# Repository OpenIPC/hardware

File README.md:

![OpenIPC logo][logo]

## OpenIPC hardware developments 

[][telegram]

### A collection of hardware developments by the OpenIPC team

- [One of the open board for OpenIPC](board_hi3516ev200)
- [8812AU module dock board for camera,input 6V@2A max and 28V@ 3A max](/module_38x38_r8812au_6v2a)
- [WIFI board for stacking on 20mm square hole flight controller for FPV](WIFI-BOARD)

### A collection of 3D models for use in OpenIPC projects

- [OpenIPC models on Printables site](https://www.printables.com/search/models?q=tag:openipc)
- [5 inch racer drone equipped with OpenIPC](OpenIPC-5inchRacer)

### Measure the output of RTL8812AU.
- [Measure the output of RTL8812AU](spectram)

More information about the [project][project] is available in our [website][website]
and on the [wiki][wiki].

<p align="center">

</p>

[firmware]: https://github.com/openipc/firmware/
[logo]: https://openipc.org/assets/openipc-logo-black.svg
[mit]: https://opensource.org/license/mit/
[opencollective]: https://opencollective.com/openipc
[paypal]: https://www.paypal.com/donate/?hosted_button_id=C6F7UJLA58MBS
[project]: https://github.com/openipc/
[telegram]: https://t.me/OpenIPC
[website]: https://openipc.org/
[wiki]: https://github.com/openipc/wiki/

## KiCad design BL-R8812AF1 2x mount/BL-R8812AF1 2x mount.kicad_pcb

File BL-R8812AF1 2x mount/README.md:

## A Radxa Zero 3W stackable double BL-R8812AF1 board

# Note this board has problems!

## The board is often not recognised by the Radxa on boot and needs re-plugging before it is detected by the Radxa. Sometimes it has this problem then powered by a BEC and not when powered from USB. I think this is an issue with this USB hub chip, and this issue has been reproduced by another user. I will update this page if/when a fix is found.

### The board integrates an SL2.1A USB hub chip which splits a single USB interface into 4 interfaces: two are used by the WiFi modules, and two additional ones are broken out for use with anything else (keyboard for configuration, USB stick, more WiFi dongles etc.).

## HOW TO MAKE
### You can order the PCB by sending the gerber files in the .zip to a PCB manufacturer. I have also included the source Kicad project files if you want to make any modifications.

<p align="center">

</p>

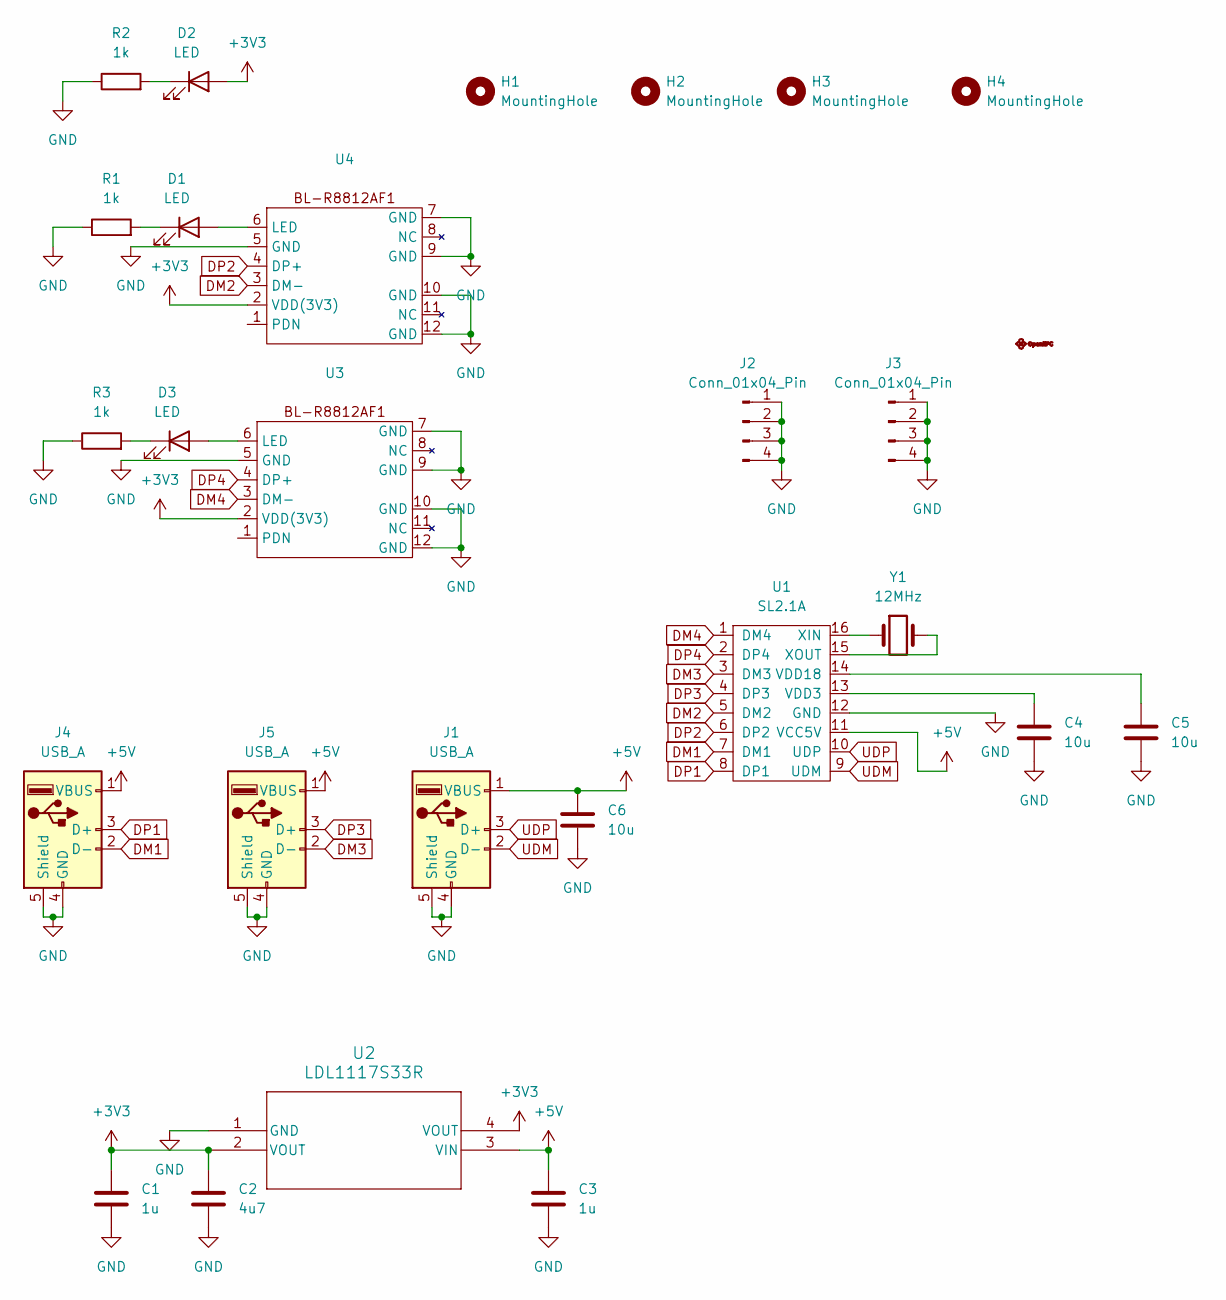
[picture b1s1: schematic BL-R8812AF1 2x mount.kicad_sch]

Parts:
C1, C3: 1u; C_0603_1608Metric_Pad1.08x0.95mm_HandSolder; LCSC C15849
C2: 4u7; C_0603_1608Metric_Pad1.08x0.95mm_HandSolder; LCSC C1705
C4, C5, C6: 10u; C_0603_1608Metric_Pad1.08x0.95mm_HandSolder; LCSC C92487
D1, D2, D3: LED; LED_0603_1608Metric_Pad1.05x0.95mm_HandSolder; LCSC C84267
H1, H2, H3, H4: MountingHole; MountingHole_4mm
J1, J4, J5: USB_A; USB_A_Molex_67643_Horizontal
J2, J3: Conn_01x04_Pin; PinHeader_1x04_P2.54mm_Vertical
R1, R2, R3: 1k; R_0603_1608Metric_Pad0.98x0.95mm_HandSolder; LCSC C21190
U1: SL2.1A; SOIC-16_4.55x10.3mm_P1.27mm; LCSC C192893
U2: LDL1117S33R; SOT223_STM; LCSC C435835
U3, U4: BL-R8812AF1
Y1: 12MHz; Crystal_SMD_5032-2Pin_5.0x3.2mm; LCSC C112573

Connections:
+3V3: C1.1, C2.1, D2.2 (A), U2.2 (VOUT), U2.4 (VOUT), U3.2 (VDD(3V3)), U4.2 (VDD(3V3))
+5V: C3.1, C6.1, J1.1 (VBUS), J4.1 (VBUS), J5.1 (VBUS), U1.11 (VCC5V), U2.3 (VIN)
DM1: J4.2 (D-), U1.7 (DM1)
DM2: U1.5 (DM2), U4.3 (DM-)
DM3: J5.2 (D-), U1.3 (DM3)
DM4: U1.1 (DM4), U3.3 (DM-)
DP1: J4.3 (D+), U1.8 (DP1)
DP2: U1.6 (DP2), U4.4 (DP+)
DP3: J5.3 (D+), U1.4 (DP3)
DP4: U1.2 (DP4), U3.4 (DP+)
GND: C1.2, C2.2, C3.2, C4.2, C5.2, C6.2, J1.4 (GND), J1.5 (Shield), J2.1, J2.2, J2.3, J2.4, J3.1, J3.2, J3.3, J3.4, J4.4 (GND), J4.5 (Shield), J5.4 (GND), J5.5 (Shield), R1.1, R2.1, R3.1, U1.12 (GND), U2.1 (GND), U3.5 (GND), U3.7 (GND), U3.9 (GND), U3.10 (GND), U3.12 (GND), U4.5 (GND), U4.7 (GND), U4.9 (GND), U4.10 (GND), U4.12 (GND)
unnamed: D1.2 (A), U4.6 (LED)
unnamed: D1.1 (K), R1.2
unnamed: D2.1 (K), R2.2
unnamed: D3.2 (A), U3.6 (LED)
unnamed: D3.1 (K), R3.2
unnamed: C4.1, U1.13 (VDD3)
unnamed: C5.1, U1.14 (VDD18)
unnamed: U1.16 (XIN), Y1.1
unnamed: U1.15 (XOUT), Y1.2
UDM: J1.2 (D-), U1.9 (UDM)
UDP: J1.3 (D+), U1.10 (UDP)

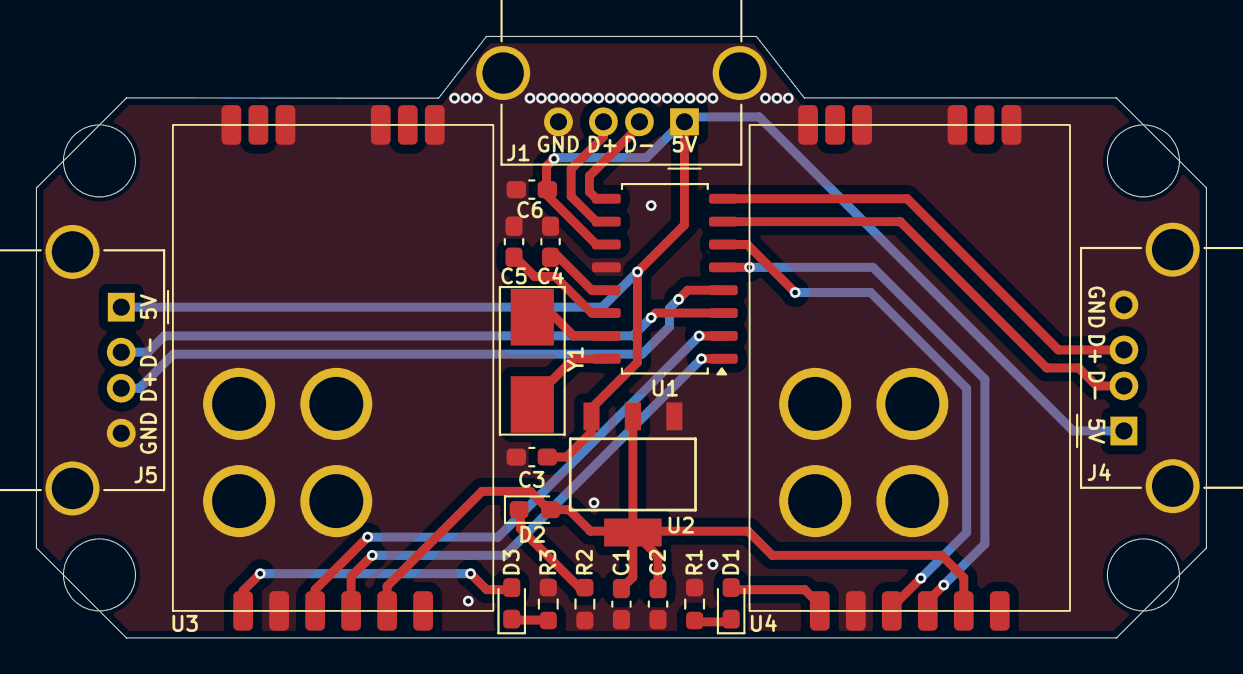
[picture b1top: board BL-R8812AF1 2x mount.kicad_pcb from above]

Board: 2 copper layers, 65.0 x 33.4 mm, 26 parts (0 on the bottom side), 22 nets.

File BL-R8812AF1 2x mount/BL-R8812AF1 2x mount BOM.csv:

Reference,Value,Footprint,Qty,LCSC
"C1,C3",1u,Capacitor_SMD:C_0603_1608Metric_Pad1.08x0.95mm_HandSolder,2,C15849
C2,4u7,Capacitor_SMD:C_0603_1608Metric_Pad1.08x0.95mm_HandSolder,1,C1705
"C4,C5,C6",10u,Capacitor_SMD:C_0603_1608Metric_Pad1.08x0.95mm_HandSolder,3,  C92487
"D1,D2,D3",LED,LED_SMD:LED_0603_1608Metric_Pad1.05x0.95mm_HandSolder,3,C84267
"R1,R2,R3",1k,Resistor_SMD:R_0603_1608Metric_Pad0.98x0.95mm_HandSolder,3,C21190
U1,SL2.1A,Package_SO:SOIC-16_4.55x10.3mm_P1.27mm,1,C192893
U2,LDL1117S33R,LDL1117S33R:SOT223_STM,1,C435835
Y1,12MHz,Crystal:Crystal_SMD_5032-2Pin_5.0x3.2mm,1,  C112573

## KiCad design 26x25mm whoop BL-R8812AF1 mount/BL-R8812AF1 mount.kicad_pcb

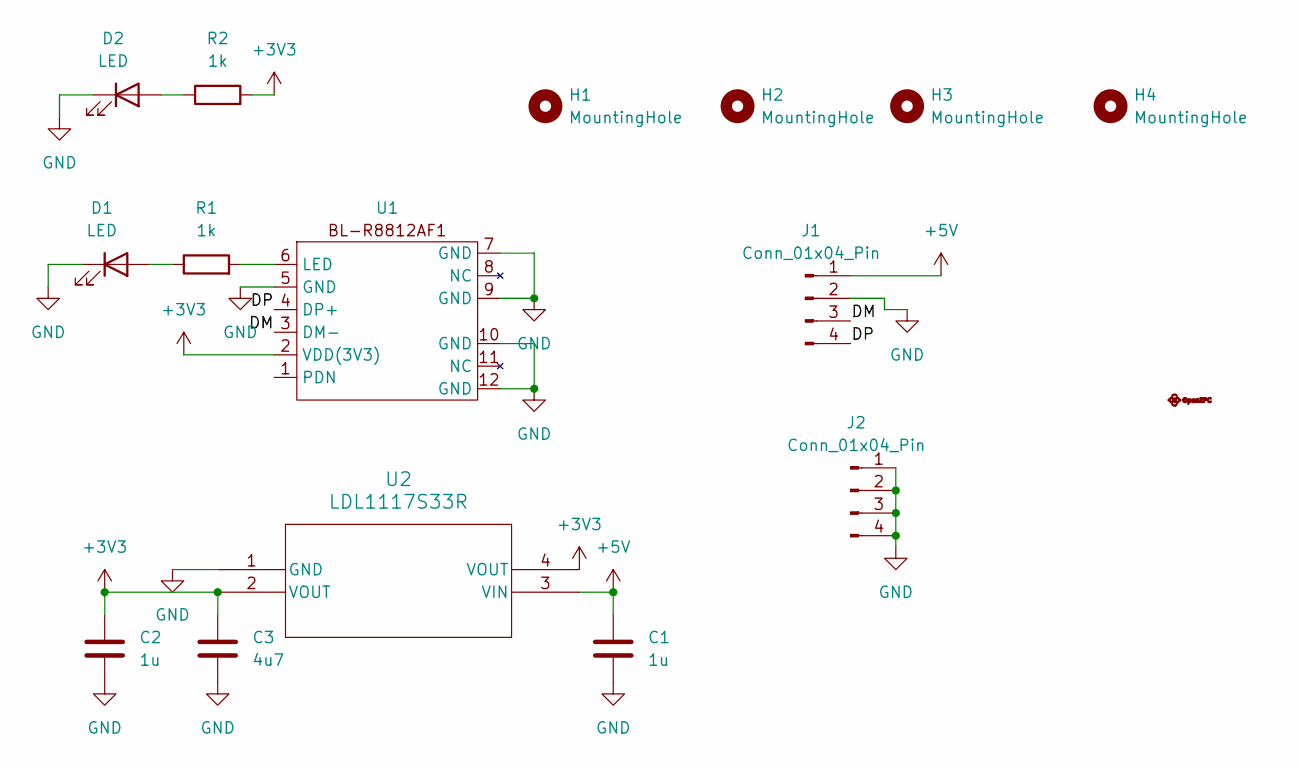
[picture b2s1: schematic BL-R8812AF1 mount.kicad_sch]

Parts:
C1, C2: 1u; C_0603_1608Metric_Pad1.08x0.95mm_HandSolder
C3: 4u7; C_0603_1608Metric_Pad1.08x0.95mm_HandSolder
D1, D2: LED; LED_0603_1608Metric_Pad1.05x0.95mm_HandSolder
H1, H2, H3, H4: MountingHole; MountingHole_4mm
J1, J2: Conn_01x04_Pin; PinHeader_1x04_P2.54mm_Vertical
R1, R2: 1k; R_0603_1608Metric_Pad0.98x0.95mm_HandSolder
U1: BL-R8812AF1
U2: LDL1117S33R; SOT223_STM

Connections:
+3V3: C2.1, C3.1, R2.2, U1.2 (VDD(3V3)), U2.2 (VOUT), U2.4 (VOUT); also elsewhere on the board
+5V: C1.1, J1.1, U2.3 (VIN)
/DM: J1.3, U1.3 (DM-); also elsewhere on the board
/DP: J1.4, U1.4 (DP+); also elsewhere on the board
GND: C1.2, C2.2, C3.2, D1.1 (K), D2.1 (K), J1.2, J2.1, J2.2, J2.3, J2.4, U1.5 (GND), U1.7 (GND), U1.9 (GND), U1.10 (GND), U1.12 (GND), U2.1 (GND); also elsewhere on the board
unnamed: D1.2 (A), R1.1
unnamed: D2.2 (A), R2.1
unnamed 7: R1.2, U1.6 (LED); also elsewhere on the board

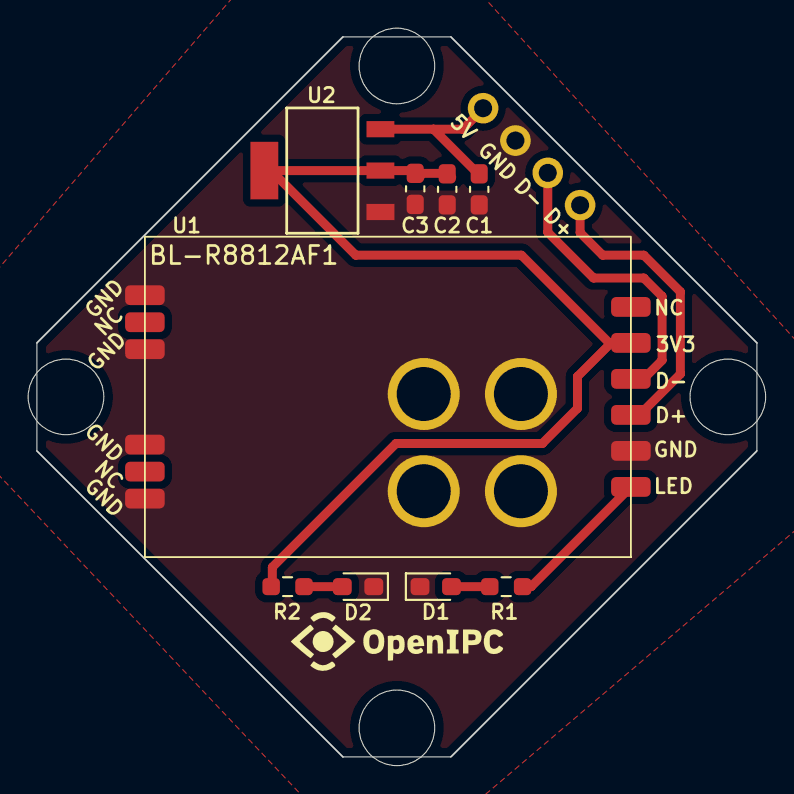
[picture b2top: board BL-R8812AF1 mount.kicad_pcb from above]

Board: 2 copper layers, 40.0 x 40.0 mm, 15 parts (0 on the bottom side), 8 nets.

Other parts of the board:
BL-R8812AF1: BL-R8812AF1

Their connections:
+3V3: BL-R8812AF1.2 (VDD(3V3)); also elsewhere on the board
/DM: BL-R8812AF1.3 (DM-); also elsewhere on the board
/DP: BL-R8812AF1.4 (DP+); also elsewhere on the board
GND: BL-R8812AF1.5 (GND), BL-R8812AF1.7 (GND), BL-R8812AF1.9 (GND), BL-R8812AF1.10 (GND), BL-R8812AF1.12 (GND); also elsewhere on the board
unnamed 7: BL-R8812AF1.6 (LED); also elsewhere on the board

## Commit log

2023-10-23 Add module_38x38_r8812au_6v2a
2023-10-23 Add board_hi3516ev200
2023-10-24 upgrade board logo
2023-10-24 28V maxinput For R8812AU 38mmx38mm board
    2S-4S lipro use
2023-10-24 Update Readme.md
    Add 28V version
2023-10-25 update board logo and Readme
2023-10-25 updates
    new cover for rtl8812au 150mw module with hole for heatsink
2023-10-25 Update README.md
    add photo cover2.stl
2023-10-27 add 28V board and connection reference
2023-10-27 Add connection reference for 28V dock board
2023-10-28 VRX models
2023-10-28 Delete hi3536_box_3d-model directory
    The project has moved to the Printables website
    https://www.printables.com/search/models?q=tag:openipc
2023-11-01 NVR board 3D model for OpenIPC
2023-11-01 3D model picture for NVR board
2023-11-14 add flash type convert for camhi and anjoy
2024-09-28 Add a whoop-size BL-R8812AF1 mount PCB
2024-10-12 Adding my double-WiFi, Radxa-stackable USB hub PCB
2024-10-12 Fixing readme
2024-10-12 Fix readme 2
2024-10-12 Fix readme 3
2024-10-12 Fix readme 4
2024-10-12 Fix readme 5
2024-10-12 Adding my double WiFi, Radxa-stackable USB hub PCB
2024-10-29 Update README.md
    Add warning about problems with the board.
